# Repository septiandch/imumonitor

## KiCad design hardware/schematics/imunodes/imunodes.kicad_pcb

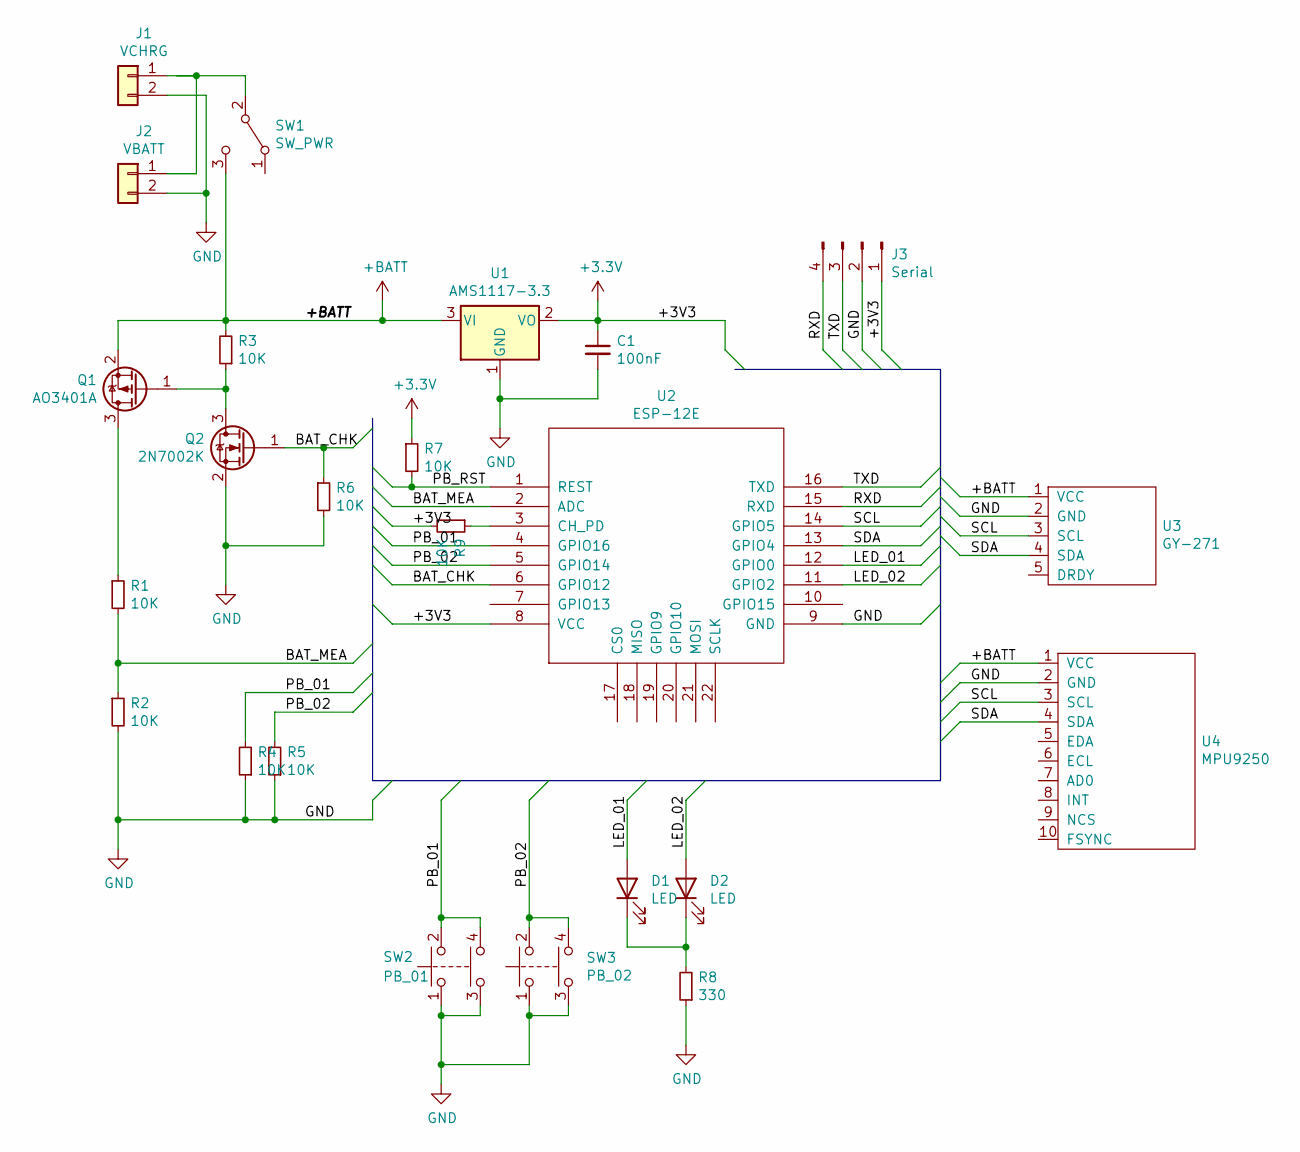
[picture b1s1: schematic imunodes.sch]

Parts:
C1: 100nF; C_1206_3216Metric
D1, D2: LED; LED_0805_2012Metric
J1: VCHRG; JST_EH_B2B-EH-A_1x02_P2.50mm_Vertical
J2: VBATT; JST_EH_B2B-EH-A_1x02_P2.50mm_Vertical
J3: Serial; PinHeader_1x04_P2.54mm_Vertical
Q1: AO3401A; SOT-23
Q2: 2N7002K; SOT-23
R1, R2, R3, R4, R5, R6, R7, R9: 10K; R_0805_2012Metric
R8: 330; R_0805_2012Metric
SW1: SW_PWR; SlideSwitch_SS12D00_1P2T_H3mm
SW2: PB_01; SW_TH_Tactile_Omron_B3F-10xx
SW3: PB_02; SW_TH_Tactile_Omron_B3F-10xx
U1: AMS1117-3.3; SOT-223-3_TabPin2
U2: ESP-12E; ESP-12E_SMD
U3: GY-271; GY271
U4: MPU9250

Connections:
+3V3: C1.1, J3.1, R7.1, R9.2, U1.2 (VO), U2.8 (VCC)
+BATT: Q1.2 (S), R3.2, SW1.3 (C), U1.3 (VI), U3.1 (VCC), U4.1 (VCC)
/BAT_CHK: Q2.1 (G), R6.1, U2.6 (GPIO12)
/BAT_MEA: R1.2, R2.1, U2.2 (ADC)
/LED_01: D1.2 (A), U2.12 (GPIO0)
/LED_02: D2.2 (A), U2.11 (GPIO2)
/PB_01: R4.2, SW2.2, SW2.4, U2.4 (GPIO16)
/PB_02: R5.2, SW3.2, SW3.4, U2.5 (GPIO14)
/PB_RST: R7.2, U2.1 (REST)
/RXD: J3.4, U2.15 (RXD)
/SCL: U2.14 (GPIO5), U3.3 (SCL), U4.3 (SCL)
/SDA: U2.13 (GPIO4), U3.4 (SDA), U4.4 (SDA)
/TXD: J3.3, U2.16 (TXD)
GND: C1.2, J1.2, J2.2, J3.2, Q2.2 (S), R2.2, R4.1, R5.1, R6.2, R8.1, SW2.1, SW2.3, SW3.1, SW3.3, U1.1 (GND), U2.9 (GND), U3.2 (GND), U4.2 (GND)
unnamed: D1.1 (K), D2.1 (K), R8.2
unnamed: J1.1, J2.1, SW1.2 (B)
unnamed: Q1.1 (G), Q2.3 (D), R3.1
unnamed: Q1.3 (D), R1.1
unnamed: R9.1, U2.3 (CH_PD)

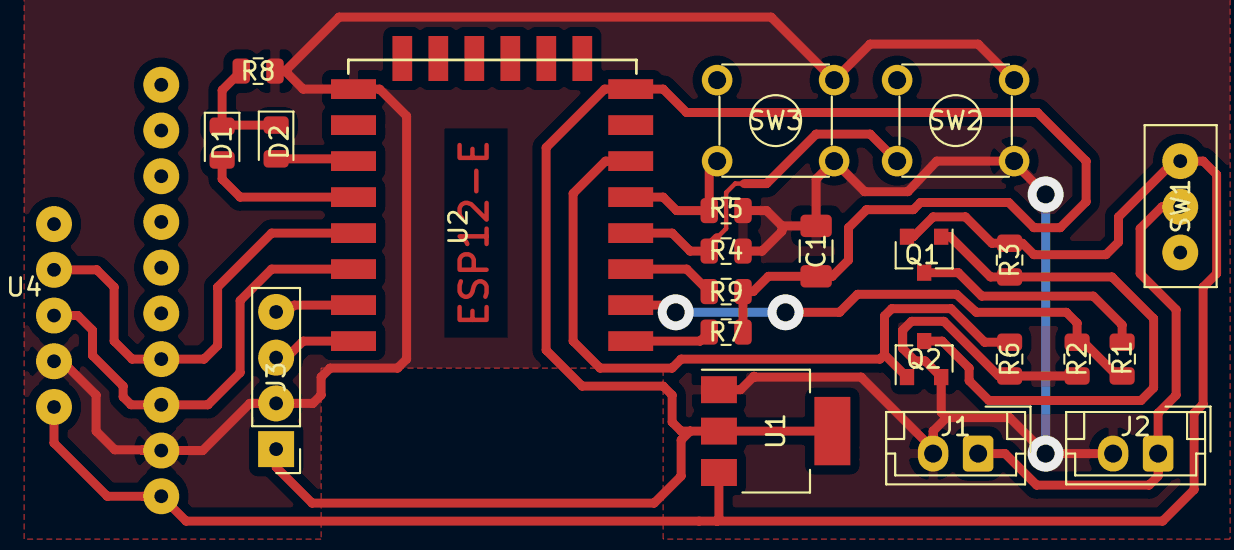
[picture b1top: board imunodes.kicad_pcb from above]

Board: 2 copper layers, 24 parts (0 on the bottom side), 19 nets.

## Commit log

2021-01-02 20210102_First Commit
2021-01-20 Mobile App progress: 80% - All Screen already implemented - BLE Read/Write - Able to receive data and draw line chart
2021-01-24 **[ New ]** - Sensor Monitor view - Bottom Sheet view
    **[ Fixes ]**
    - Received Value conversion bug fix
    - Linechart view improvement
    - Dummy registration fix
    - Sensor Monitor initial dummy value fix
2021-01-27 [New] - Shared Prefferences - Horizontal Number Picker for setting values - User Data Updates - OWAS data base
    [Fixed]
    - Received values conversion fix
    - BLE Device Screen return without selected device bug fix
2021-01-30 OWAS Monitor Updates
    Update colorscheme.dart, owas.dart, and 2 more files...
2021-01-31 Support BackEnd Connection
    [New]
    - Database write (post method)
    [Bug Fixes]
    -
2021-02-05 Support Next-Previous Database read
2021-03-23 Add Freecad Enclosure Drawing
2021-03-23 Mobile App 75%
2021-03-23 Firmware 90%
2021-04-14 New Structure: Separate as ImuNodes and ImuServer
2021-04-25 MobileApp Changes
    Multiple submission bug fixes, Setting iniitial value bug fixes, and some improvements
2021-04-25 ImuNodes & ImuServer Fixes
    GET request improvement so no node data can be retrieved sequentially
2021-04-25 ImuServer Case
    Cover to attach the device to Battery case
2021-04-25 Multiple Data Submission
    Show table for sensor log
2021-04-25 Apply Custom Icon
    Generate using :
    flutter pub pub run flutter_launcher_icons:main
2021-06-19 WebServer now shown as JSON format
    Using ArduinoJson library
2021-06-19 Setting List Generation Fixes
    Fix false setting value generation
2021-07-10 ESP32 Support
    Change ESP32 as sensor node and alarm function
2021-07-10 Desktop App First Commit
    Migration from Mobile app
2021-11-16 It works !
    - Desktop App Added
    - ImuServer deletion (all working as node, use dedicated access point)
2021-11-16 MPU6500 MPU9250 Switch Fixes
2021-11-27 Date Label fix, Legs OWAS Change (still in progress)
2021-11-30 Leg OWAS Judgement Update
2021-12-05 Leg OWAS Judgement update & tested
